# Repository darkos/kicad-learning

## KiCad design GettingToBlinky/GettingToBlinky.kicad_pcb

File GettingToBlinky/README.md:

# KiCad learning

This is repository of various preactice-playing lessons about KiCad.

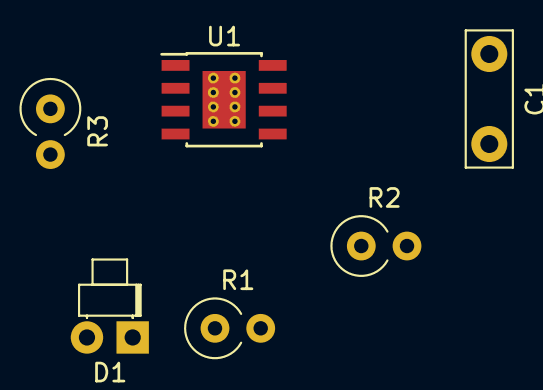
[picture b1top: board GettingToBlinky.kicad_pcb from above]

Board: 2 copper layers, 6 parts (0 on the bottom side), 6 nets, no tracks yet.

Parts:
C1: 1mF; C_Disc_D7.5mm_W2.5mm_P5.00mm
D1: LED; LED_D1.8mm_W1.8mm_H2.4mm_Horizontal_O1.27mm_Z8.2mm
R1, R3: 1K; R_Axial_DIN0309_L9.0mm_D3.2mm_P2.54mm_Vertical
R2: 470K; R_Axial_DIN0309_L9.0mm_D3.2mm_P2.54mm_Vertical
U1: 7555; HTSOP-8-1EP_3.9x4.9mm_Pitch1.27mm_ThermalVias

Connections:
/VDD: R1.1, U1.4, U1.8
GND: C1.2, D1.1, U1.1, U1.5
unnamed: C1.1, R2.2, U1.2, U1.6
unnamed: D1.2, R3.2
unnamed: R1.2, R2.1, U1.7
unnamed: R3.1, U1.3

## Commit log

2018-06-02 initial comit
2018-06-02 adding README
2018-06-02 autorouting
2018-06-03 gitignore
2018-06-03 vulcan prepamp initial commit
2018-07-18 ignoring *bak and removing old baks
2018-07-30 schema
